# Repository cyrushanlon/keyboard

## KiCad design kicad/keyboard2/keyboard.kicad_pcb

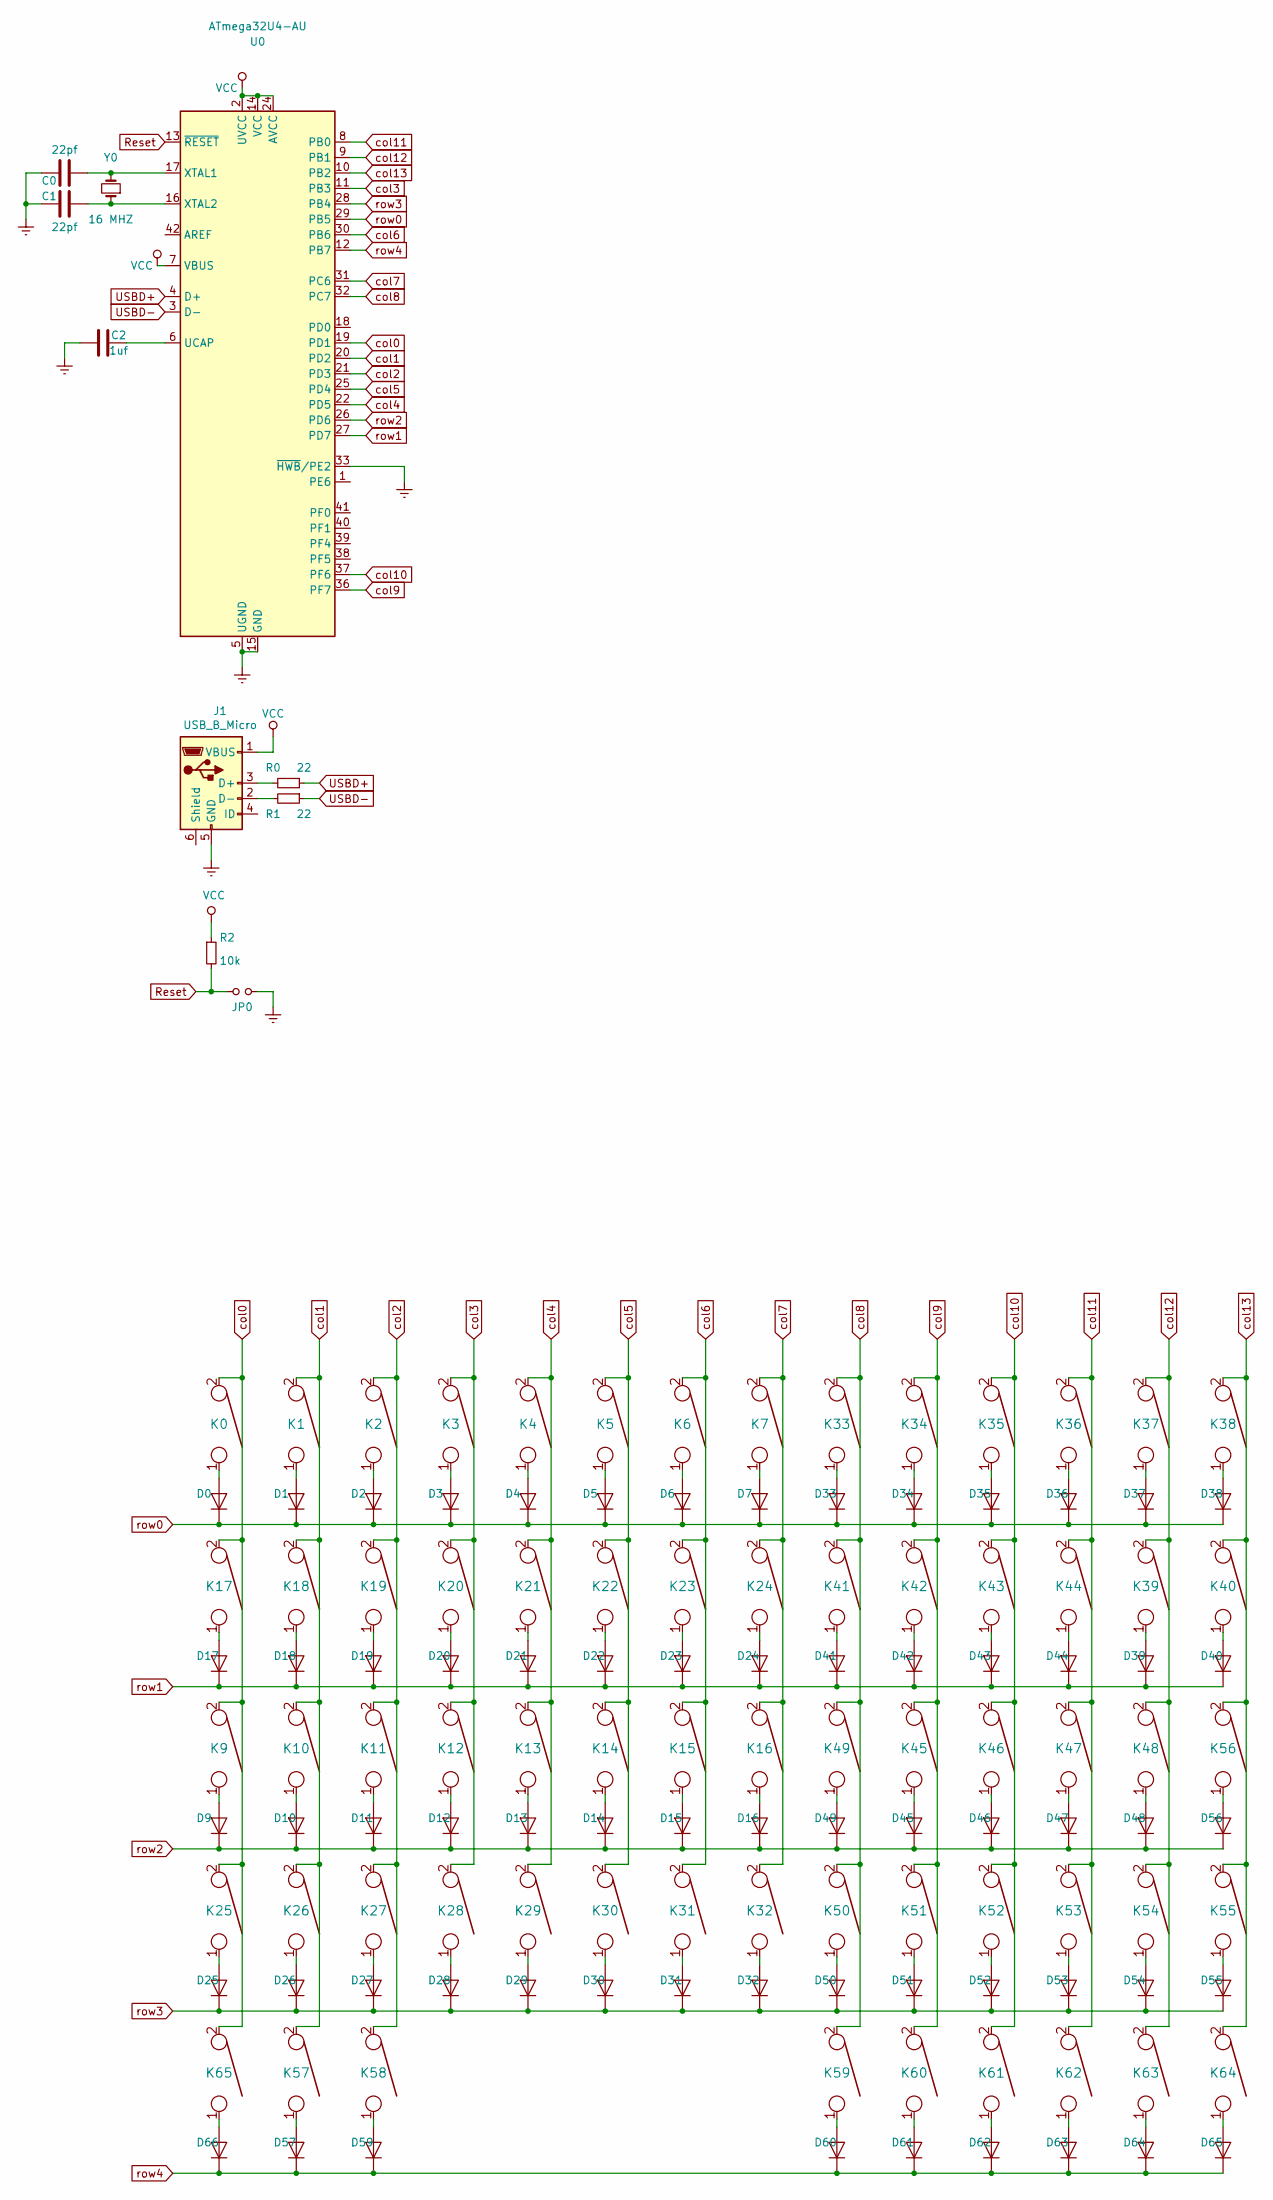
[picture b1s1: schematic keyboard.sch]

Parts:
C0, C1: 22pf; C_1206_3216Metric_Pad1.42x1.75mm_HandSolder
C2: 1uf; C_1206_3216Metric_Pad1.42x1.75mm_HandSolder
D0, D1, D2, D3, D4, D5, D6, D7, D9, D10, D11, D12, D13, D14, D15, D16, D17, D18, D19, D20, D21, D22, D23, D24, D25, D26, D27, D28, D29, D30, D31, D32, D33, D34, D35, D36, D37, D38, D39, D40, D41, D42, D43, D44, D45, D46, D47, D48, D49, D50, D51, D52, D53, D54, D55, D56, D57, D59, D60, D61, D62, D63, D64, D65, D66: D; D_T-1_P5.08mm_Horizontal
J1: USB_B_Micro; USB_microB
JP0: SW_DIP_SPSTx01_Slide_6.7x4.1mm_W7.62mm_P2.54mm_LowProfile
K0, K1, K2, K3, K4, K5, K6, K7, K9, K10, K11, K12, K13, K14, K15, K16, K17, K18, K19, K20, K21, K22, K23, K24, K25, K26, K27, K28, K29, K30, K31, K32, K33, K34, K35, K36, K37, K38, K39, K40, K41, K42, K43, K44, K45, K46, K47, K48, K49, K50, K51, K52, K53, K54, K55, K56, K57, K58, K59, K60, K61, K62, K63, K64, K65: KEYSW; Kailh_socket
R0, R1: 22; R_1206_3216Metric_Pad1.42x1.75mm_HandSolder
R2: 10k; R_1206_3216Metric_Pad1.42x1.75mm_HandSolder
U0: ATmega32U4-AU; TQFP-44_10x10mm_P0.8mm
Y0: 16 MHZ; Crystal_SMD_Abracon_ABM3-2Pin_5.0x3.2mm_HandSoldering

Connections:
Earth: C0.2, C1.2, C2.2, J1.5 (GND), JP0.2, U0.5 (UGND), U0.15 (GND), U0.23 (GND), U0.33 (~HWB~/PE2), U0.35 (GND), U0.43 (GND)
unnamed: C0.1, U0.17 (XTAL1), Y0.2
unnamed: C1.1, U0.16 (XTAL2), Y0.1
unnamed: C2.1, U0.6 (UCAP)
unnamed: D0.2 (A), K0.1
unnamed: D1.2 (A), K1.1
unnamed: D2.2 (A), K2.1
unnamed: D3.2 (A), K3.1
unnamed: D4.2 (A), K4.1
unnamed: D5.2 (A), K5.1
unnamed: D6.2 (A), K6.1
unnamed: D7.2 (A), K7.1
unnamed: D9.2 (A), K9.1
unnamed: D10.2 (A), K10.1
unnamed: D11.2 (A), K11.1
unnamed: D12.2 (A), K12.1
unnamed: D13.2 (A), K13.1
unnamed: D14.2 (A), K14.1
unnamed: D15.2 (A), K15.1
unnamed: D16.2 (A), K16.1
unnamed: D17.2 (A), K17.1
unnamed: D18.2 (A), K18.1
unnamed: D19.2 (A), K19.1
unnamed: D20.2 (A), K20.1
unnamed: D21.2 (A), K21.1
unnamed: D22.2 (A), K22.1
unnamed: D23.2 (A), K23.1
unnamed: D24.2 (A), K24.1
unnamed: D25.2 (A), K25.1
unnamed: D26.2 (A), K26.1
unnamed: D27.2 (A), K27.1
unnamed: D28.2 (A), K28.1
unnamed: D29.2 (A), K29.1
unnamed: D30.2 (A), K30.1
unnamed: D31.2 (A), K31.1
unnamed: D32.2 (A), K32.1
unnamed: D33.2 (A), K33.1
unnamed: D34.2 (A), K34.1
unnamed: D35.2 (A), K35.1
unnamed: D36.2 (A), K36.1
unnamed: D37.2 (A), K37.1
unnamed: D38.2 (A), K38.1
unnamed: D39.2 (A), K39.1
unnamed: D40.2 (A), K40.1
unnamed: D41.2 (A), K41.1
unnamed: D42.2 (A), K42.1
unnamed: D43.2 (A), K43.1
unnamed: D44.2 (A), K44.1
unnamed: D45.2 (A), K45.1
unnamed: D46.2 (A), K46.1
unnamed: D47.2 (A), K47.1
unnamed: D48.2 (A), K48.1
unnamed: D49.2 (A), K49.1
unnamed: D50.2 (A), K50.1
unnamed: D51.2 (A), K51.1
unnamed: D52.2 (A), K52.1
unnamed: D53.2 (A), K53.1
unnamed: D54.2 (A), K54.1
unnamed: D55.2 (A), K55.1
unnamed: D56.2 (A), K56.1
unnamed: D57.2 (A), K57.1
unnamed: D59.2 (A), K58.1
unnamed: D60.2 (A), K59.1
unnamed: D61.2 (A), K60.1
unnamed: D62.2 (A), K61.1
unnamed: D63.2 (A), K62.1
unnamed: D64.2 (A), K63.1
unnamed: D65.2 (A), K64.1
unnamed: D66.2 (A), K65.1
unnamed: J1.2 (D-), R1.2
unnamed: J1.3 (D+), R0.2
Reset: JP0.1, R2.2, U0.13 (~RESET)
USBD+: R0.1, U0.4 (D+)
USBD-: R1.1, U0.3 (D-)
VCC: J1.1 (VBUS), R2.1, U0.2 (UVCC), U0.7 (VBUS), U0.14 (VCC), U0.24 (AVCC), U0.34 (VCC), U0.44 (AVCC)
col0: K0.2, K9.2, K17.2, K25.2, K65.2, U0.19 (PD1)
col1: K1.2, K10.2, K18.2, K26.2, K57.2, U0.20 (PD2)
col2: K2.2, K11.2, K19.2, K27.2, K58.2, U0.21 (PD3)
col3: K3.2, K12.2, K20.2, K28.2, U0.11 (PB3)
col4: K4.2, K13.2, K21.2, K29.2, U0.22 (PD5)
col5: K5.2, K14.2, K22.2, K30.2, U0.25 (PD4)
col6: K6.2, K15.2, K23.2, K31.2, U0.30 (PB6)
col7: K7.2, K16.2, K24.2, K32.2, U0.31 (PC6)
col8: K33.2, K41.2, K49.2, K50.2, K59.2, U0.32 (PC7)
col9: K34.2, K42.2, K45.2, K51.2, K60.2, U0.36 (PF7)
col10: K35.2, K43.2, K46.2, K52.2, K61.2, U0.37 (PF6)
col11: K36.2, K44.2, K47.2, K53.2, K62.2, U0.8 (PB0)
col12: K37.2, K39.2, K48.2, K54.2, K63.2, U0.9 (PB1)
col13: K38.2, K40.2, K55.2, K56.2, K64.2, U0.10 (PB2)
row0: D0.1 (K), D1.1 (K), D2.1 (K), D3.1 (K), D4.1 (K), D5.1 (K), D6.1 (K), D7.1 (K), D33.1 (K), D34.1 (K), D35.1 (K), D36.1 (K), D37.1 (K), D38.1 (K), U0.29 (PB5)
row1: D17.1 (K), D18.1 (K), D19.1 (K), D20.1 (K), D21.1 (K), D22.1 (K), D23.1 (K), D24.1 (K), D39.1 (K), D40.1 (K), D41.1 (K), D42.1 (K), D43.1 (K), D44.1 (K), U0.27 (PD7)
row2: D9.1 (K), D10.1 (K), D11.1 (K), D12.1 (K), D13.1 (K), D14.1 (K), D15.1 (K), D16.1 (K), D45.1 (K), D46.1 (K), D47.1 (K), D48.1 (K), D49.1 (K), D56.1 (K), U0.26 (PD6)
row3: D25.1 (K), D26.1 (K), D27.1 (K), D28.1 (K), D29.1 (K), D30.1 (K), D31.1 (K), D32.1 (K), D50.1 (K), D51.1 (K), D52.1 (K), D53.1 (K), D54.1 (K), D55.1 (K), U0.28 (PB4)
row4: D57.1 (K), D59.1 (K), D60.1 (K), D61.1 (K), D62.1 (K), D63.1 (K), D64.1 (K), D65.1 (K), D66.1 (K), U0.12 (PB7)

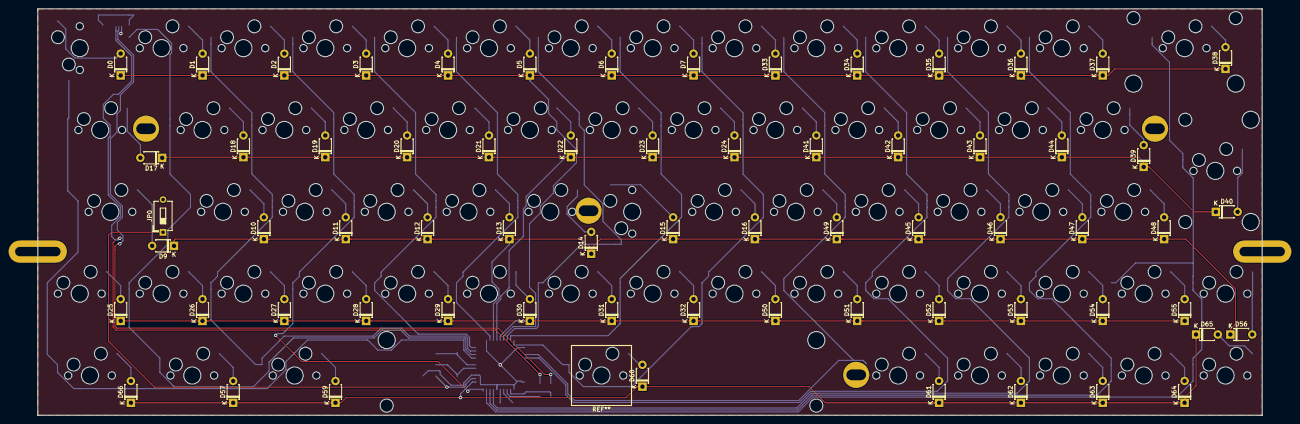
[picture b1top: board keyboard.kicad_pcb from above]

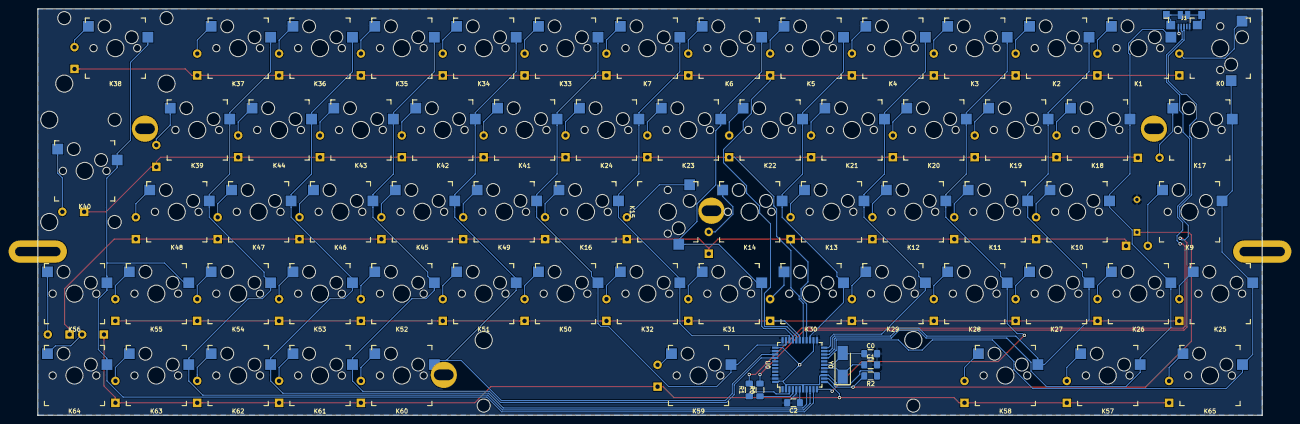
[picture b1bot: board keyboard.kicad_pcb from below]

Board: 2 copper layers, 285.0 x 94.6 mm, 146 parts (9 on the bottom side), 94 nets.

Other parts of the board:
Poker_oval_hole: VAL**; Poker_oval_hole
Poker_oval_hole#2, Poker_oval_hole#3, Poker_oval_hole#4: VAL**; Poker_oval_hole
Poker_side_edge_long: VAL**; Poker_side_edge_long
Poker_side_edge_long#2: VAL**; Poker_side_edge_long

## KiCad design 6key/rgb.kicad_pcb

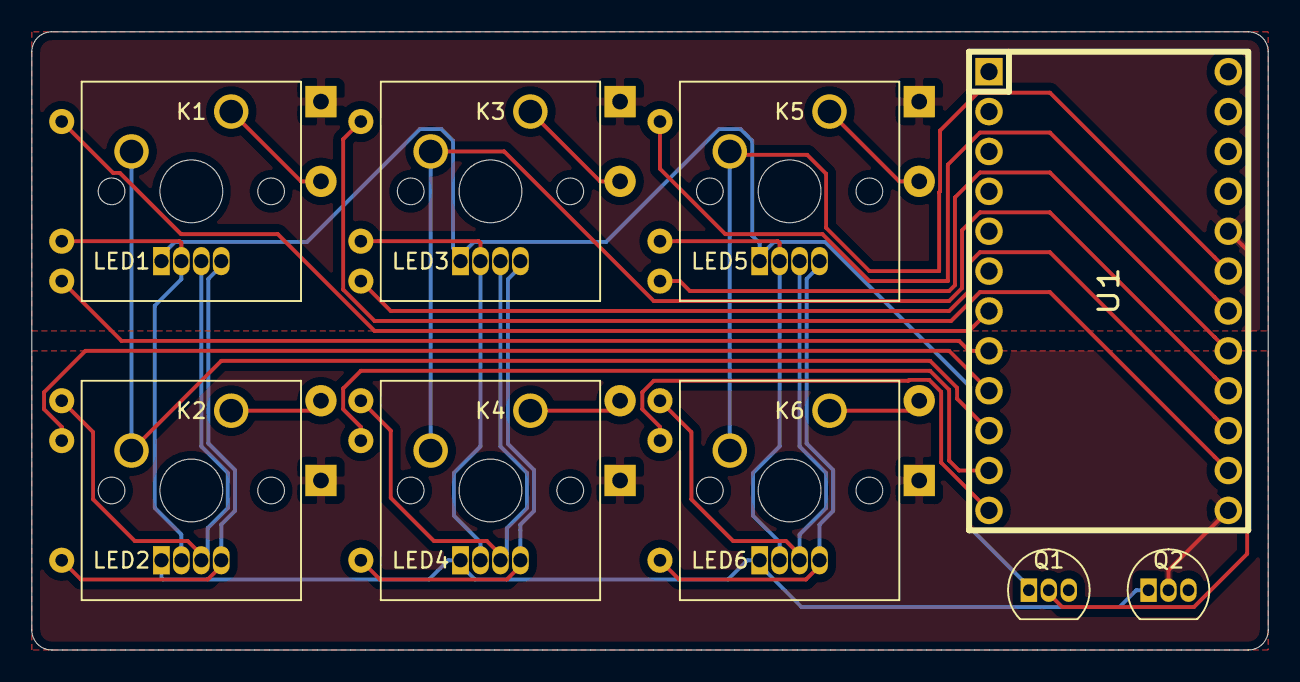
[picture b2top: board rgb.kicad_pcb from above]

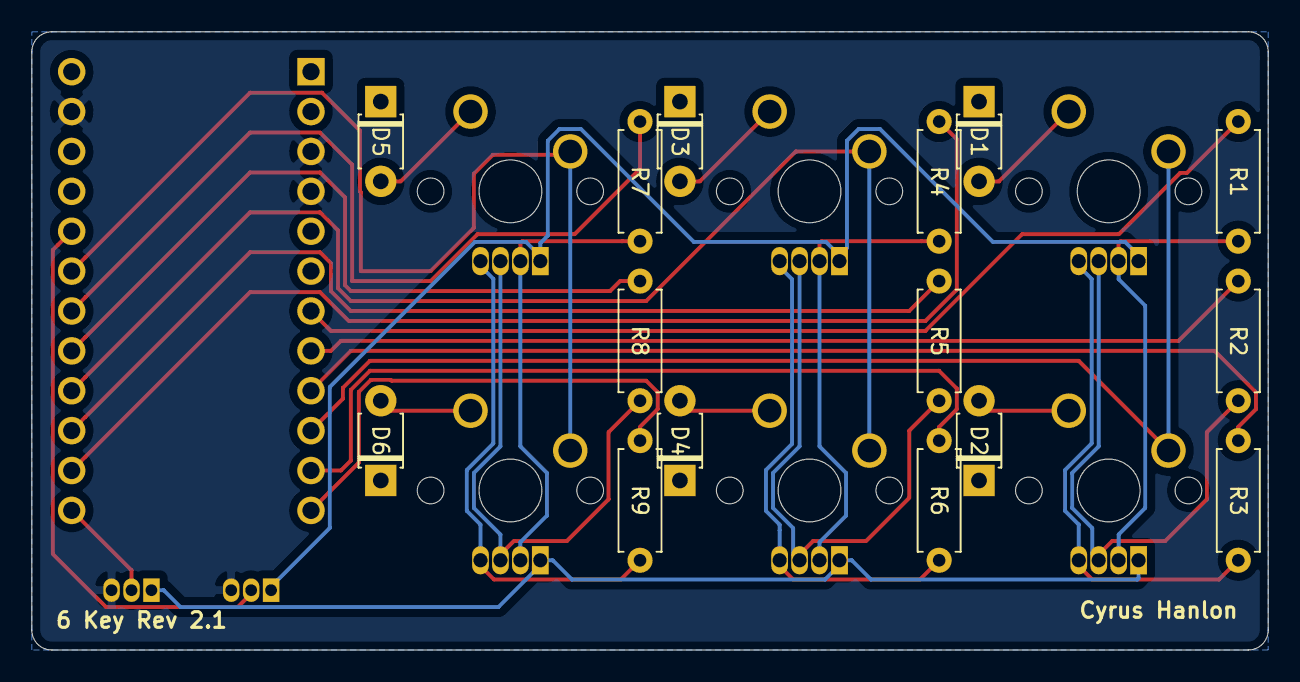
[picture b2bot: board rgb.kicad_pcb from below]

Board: 2 copper layers, 78.7 x 39.4 mm, 30 parts (15 on the bottom side), 32 nets.

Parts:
D1, D2, D3, D4, D5, D6: D; D_T-1_P5.08mm_Horizontal
K1, K2, K3, K4, K5, K6: KEYSW; SW_Cherry_MX_1.00u_PCB
LED1, LED2, LED3, LED4, LED5, LED6: LED_CRGB; LED_D5.0mm-4_RGB_NO_CASE
Q1, Q2: BF244A; TO-92_Inline
R1, R2, R3, R4, R5, R6, R7, R8, R9: R; R_Axial_DIN0207_L6.3mm_D2.5mm_P7.62mm_Horizontal
U1: ProMicro; Pro_Micro

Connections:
GND: Q1.3, Q2.3, U1.3, U1.4, U1.23
unnamed: D1.2, K1.1
unnamed: D2.2, K2.1
unnamed: D3.2, K3.1
unnamed: D4.2, K4.1
unnamed: D5.2, K5.1
unnamed: D6.2, K6.1
unnamed: LED1.1, LED3.1, LED5.1, Q1.1
unnamed: LED1.2, LED2.2, R1.2
unnamed: LED1.3, LED2.3, R2.2
unnamed: LED1.4, LED2.4, R3.2
unnamed: LED2.1, LED4.1, LED6.1, Q2.1
unnamed: LED3.2, LED4.2, R4.2
unnamed: LED3.3, LED4.3, R5.2
unnamed: LED3.4, LED4.4, R6.2
unnamed: LED5.2, LED6.2, R7.2
unnamed: LED5.3, LED6.3, R8.2
unnamed: LED5.4, LED6.4, R9.2
col0: K1.2, K2.2, U1.10
col1: K3.2, K4.2, U1.16
col2: K5.2, K6.2, U1.19
led0b: R3.1, U1.9
led0g: R2.1, U1.8
led0r: R1.1, U1.7
led1b: R6.1, U1.11
led1g: R5.1, U1.15
led1r: R4.1, U1.14
led2b: R9.1, U1.12
led2g: R8.1, U1.17
led2r: R7.1, U1.18
row0: D1.1, D3.1, D5.1, Q1.2, U1.20
row1: D2.1, D4.1, D6.1, Q2.2, U1.13

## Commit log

2019-09-10 shift reg arduino, 2x3 rgb pcb
2019-09-17 4x4 rgb led matrix
2019-11-15 reshuffled repo layout, added first version of pcb keyboard
2019-11-27 moved libs to shared location, worked on 2x3 firmware, started work on full 65 key
2019-11-28 added screw holes, positioned switches on pcb
2019-12-17 changed circuit to 5x13, designed pcb
2019-12-17 flipped arduino to other side
2020-02-24 started work on removing arduino board and using 32U4 directly
2020-02-25 completed main layout
2020-02-28 Completed first attempt at keyboard2 tracks
2020-12-17 add initial version of firmware for 65 key keeb
